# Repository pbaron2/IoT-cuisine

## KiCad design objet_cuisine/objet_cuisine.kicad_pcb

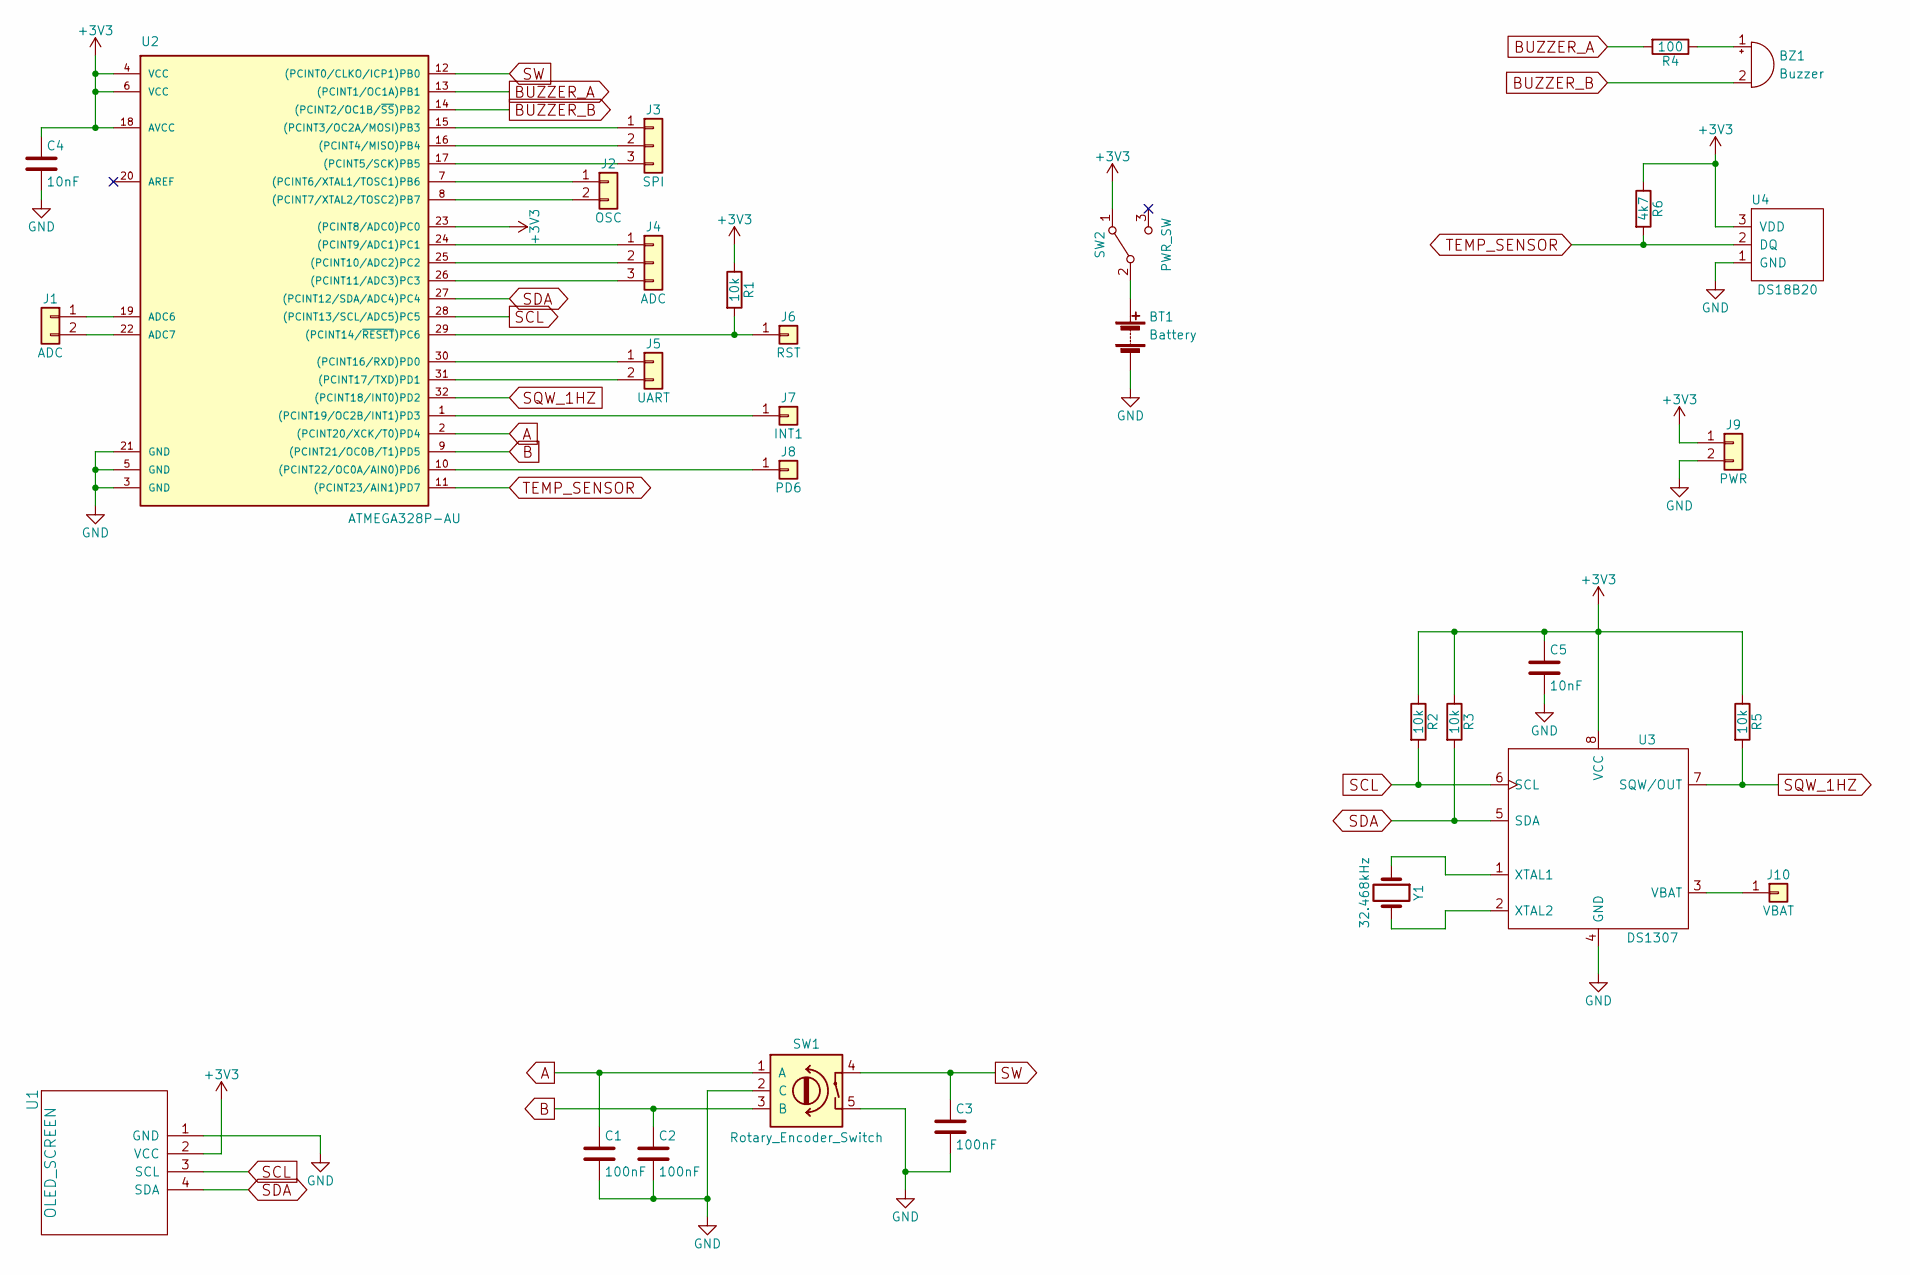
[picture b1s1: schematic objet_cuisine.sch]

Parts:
BT1: Battery; Keystone_2468_2xAAA
BZ1: Buzzer; Buzzer_12x9.5RM7.6
C1, C2, C3: 100nF; C_Disc_D5.0mm_W2.5mm_P5.00mm
C4, C5: 10nF; C_0603_HandSoldering
J1: ADC; Pin_Header_Straight_1x02_Pitch2.54mm
J2: OSC; Pin_Header_Straight_1x02_Pitch2.54mm
J3: SPI; Pin_Header_Straight_1x03_Pitch2.54mm
J4: ADC; Pin_Header_Straight_1x03_Pitch2.54mm
J5: UART; Pin_Header_Straight_1x02_Pitch2.54mm
J6: RST; Pin_Header_Straight_1x01_Pitch2.54mm
J7: INT1; Pin_Header_Straight_1x01_Pitch2.54mm
J8: PD6; Pin_Header_Straight_1x01_Pitch2.54mm
J9: PWR; Pin_Header_Straight_1x02_Pitch2.54mm
J10: VBAT; Pin_Header_Straight_1x01_Pitch2.54mm
R1, R2, R3, R5: 10k; R_0805_HandSoldering
R4: 100; R_Axial_DIN0309_L9.0mm_D3.2mm_P15.24mm_Horizontal
R6: 4k7; R_Axial_DIN0309_L9.0mm_D3.2mm_P15.24mm_Horizontal
SW1: Rotary_Encoder_Switch; Rotary_Encoder
SW2: PWR_SW; SW_CuK_OS102011MA1QN1_SPDT_Angled
U1: OLED_SCREEN; Pin_Header_Straight_1x04_Pitch2.54mm
U2: ATMEGA328P-AU; TQFP-32_7x7mm_Pitch0.8mm
U3: DS1307; SO-8_5.3x6.2mm_Pitch1.27mm
U4: DS18B20; Pin_Header_Straight_1x03_Pitch2.54mm
Y1: 32.468kHz; Crystal_AT310_d3.0mm_l10.0mm_Horizontal

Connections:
+3V3: C4.1, C5.1, J9.1, R1.1, R2.1, R3.1, R5.1, R6.1, SW2.1 (A), U1.2 (VCC), U2.4 (VCC), U2.6 (VCC), U2.18 (AVCC), U2.23 ((PCINT8/ADC0)PC0), U3.8 (VCC), U4.3 (VDD)
A: C1.1, SW1.1 (A), U2.2 ((PCINT20/XCK/T0)PD4)
B: C2.1, SW1.3 (B), U2.9 ((PCINT21/OC0B/T1)PD5)
BUZZER_A: R4.2, U2.13 ((PCINT1/OC1A)PB1)
BUZZER_B: BZ1.2 (+), U2.14 ((PCINT2/OC1B/~SS~)PB2)
GND: BT1.2 (-), C1.2, C2.2, C3.2, C4.2, C5.2, J9.2, SW1.2 (C), SW1.5, U1.1 (GND), U2.3 (GND), U2.5 (GND), U2.21 (GND), U3.4 (GND), U4.1 (GND)
unnamed: BT1.1 (+), SW2.2 (B)
unnamed: BZ1.1 (-), R4.1
unnamed: J1.1, U2.19 (ADC6)
unnamed: J1.2, U2.22 (ADC7)
unnamed: J2.1, U2.7 ((PCINT6/XTAL1/TOSC1)PB6)
unnamed: J2.2, U2.8 ((PCINT7/XTAL2/TOSC2)PB7)
unnamed: J3.1, U2.15 ((PCINT3/OC2A/MOSI)PB3)
unnamed: J3.2, U2.16 ((PCINT4/MISO)PB4)
unnamed: J3.3, U2.17 ((PCINT5/SCK)PB5)
unnamed: J4.1, U2.24 ((PCINT9/ADC1)PC1)
unnamed: J4.2, U2.25 ((PCINT10/ADC2)PC2)
unnamed: J4.3, U2.26 ((PCINT11/ADC3)PC3)
unnamed: J5.1, U2.30 ((PCINT16/RXD)PD0)
unnamed: J5.2, U2.31 ((PCINT17/TXD)PD1)
unnamed: J6.1, R1.2, U2.29 ((PCINT14/~RESET~)PC6)
unnamed: J7.1, U2.1 ((PCINT19/OC2B/INT1)PD3)
unnamed: J8.1, U2.10 ((PCINT22/OC0A/AIN0)PD6)
unnamed: J10.1, U3.3 (VBAT)
unnamed: U3.1 (XTAL1), Y1.1
unnamed: U3.2 (XTAL2), Y1.2
SCL: R2.2, U1.3 (SCL), U2.28 ((PCINT13/SCL/ADC5)PC5), U3.6 (SCL)
SDA: R3.2, U1.4 (SDA), U2.27 ((PCINT12/SDA/ADC4)PC4), U3.5 (SDA)
SQW_1HZ: R5.2, U2.32 ((PCINT18/INT0)PD2), U3.7 (SQW/OUT)
SW: C3.1, SW1.4, U2.12 ((PCINT0/CLKO/ICP1)PB0)
TEMP_SENSOR: R6.2, U2.11 ((PCINT23/AIN1)PD7), U4.2 (DQ)

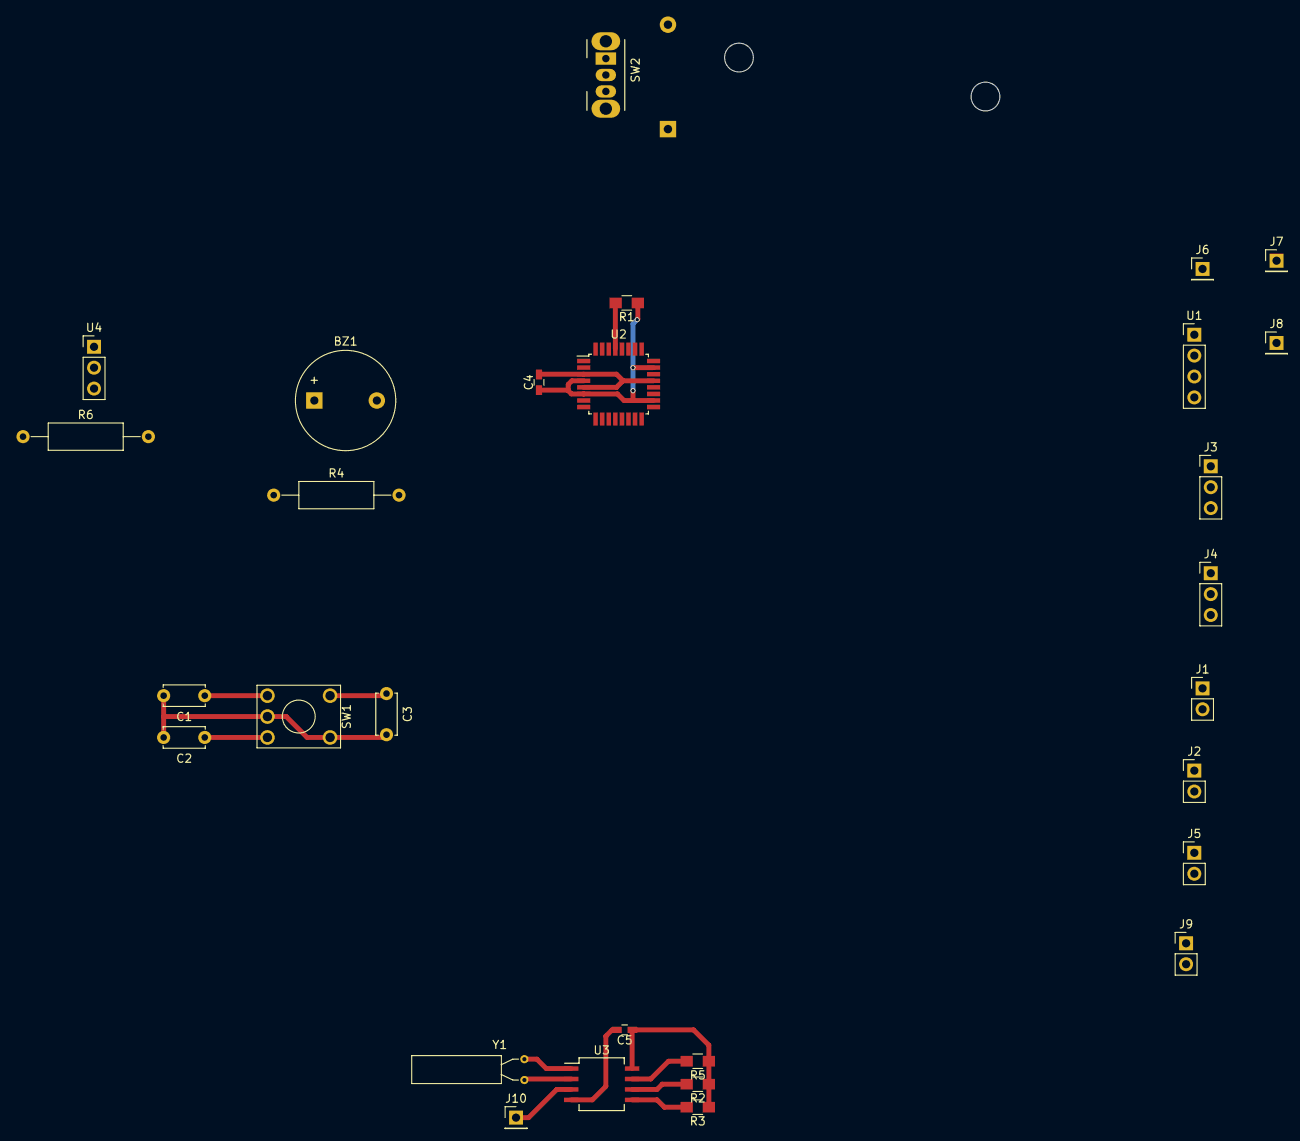
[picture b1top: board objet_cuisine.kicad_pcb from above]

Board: 2 copper layers, 30 parts (1 on the bottom side), 31 nets.

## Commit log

2020-04-12 change frequency of tone
